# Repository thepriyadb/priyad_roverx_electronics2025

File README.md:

*15/05/25*
*Task 0: Evaluation of rover technologies implemented by different teams in previous years of the University Rover Challenge (URC)*

*20/05/25*
*Task 1:* 
*Communication protocols - I2C, CAN, Relays*

*26/05/25*
*Task 1:* 
- *SSR*
- *Octocoupler*
- *Differential pair*
- *Arbitration*
- *CRC*

*2/06/25*
*Task 2:*
1. *Start with C++ basics with the W3 schools website*
2. *Start reading about an Arduino, what it is and how it functions*

*07/06/25*
*Task 3:*
- *STM32*
- *Timers & Clocks*

*08/06/25*
*Task 4:*
1. *Compare microcontrollers*
2. *PWM Signal Wave Visualization*

*17/06/25*
*Task 5:*
- *PWM*
- *Projects on Arduino*
- *Delays vs Millis*

*21/05/2025*
*Task 6:*
*Register level programming*

*15/07/2025*
*Task 7:*
*Design a schematic with a fan, an LED and Arduino using KiCAD*

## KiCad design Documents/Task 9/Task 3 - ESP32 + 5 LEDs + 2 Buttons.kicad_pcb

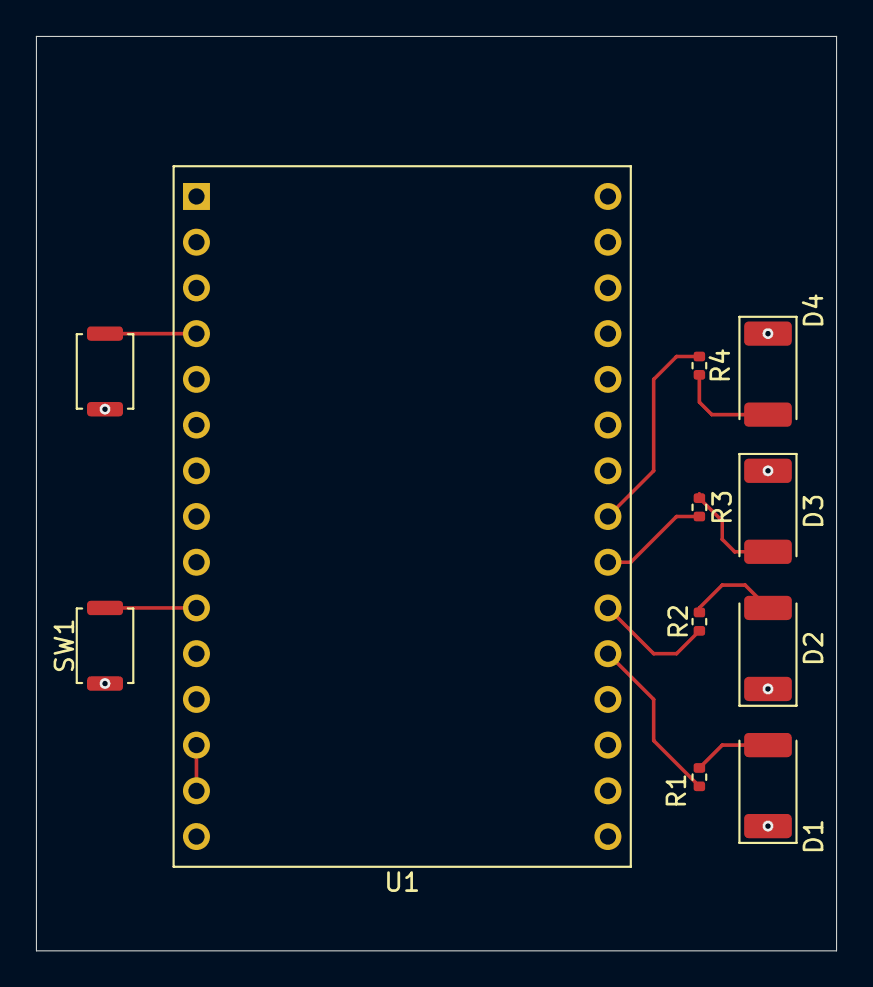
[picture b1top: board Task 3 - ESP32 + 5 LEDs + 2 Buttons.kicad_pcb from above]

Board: 2 copper layers, 44.4 x 50.8 mm, 11 parts (0 on the bottom side), 12 nets.

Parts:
D1, D2, D3, D4: LED; LED_2010_5025Metric
R1, R2, R3, R4: R; R_0402_1005Metric
SW1, SW2: SW_Push; SW_Push_SPST_NO_Alps_SKRK
U1: ESP32-C3-DevKitM-1

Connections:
+5V: U1.13 (5V), U1.14 (5V)
/LED1: R1.1, U1.20 (IO4)
/LED2: R2.1, U1.21 (IO5)
/LED3: R3.1, U1.22 (IO6)
/LED4: R4.1, U1.23 (IO7)
/SW1: SW1.2, U1.10 (IO1)
/SW2: SW2.1, U1.4 (IO2)
GND: D1.1 (K), D2.1 (K), D3.1 (K), D4.1 (K), SW1.1, SW2.2, U1.1 (GND), U1.6 (GND), U1.8 (GND), U1.12 (GND), U1.15 (GND), U1.16 (GND), U1.19 (GND), U1.24 (GND), U1.27 (GND), U1.30 (GND)
unnamed: D1.2 (A), R1.2
unnamed: D2.2 (A), R2.2
unnamed: D3.2 (A), R3.2
unnamed: D4.2 (A), R4.2

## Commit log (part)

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2025-05-29 Initial commit of Obsidian notes
2025-05-30 Update notes
2025-06-07 Updated notes
2025-06-07 images
2025-06-17 removal
2025-07-27 Create Task 9 - ESP32 + 4 LEDs + 2 Switches
2025-07-27 Update Task 9 - ESP32 + 4 LEDs + 2 Switches
2025-07-28 Rename Task 9 - ESP32 + 4 LEDs + 2 Switches to Task 9 - ESP32 + 4 LEDs + 2 Switches.md
2025-12-29 Rename .gitignore to STM32_ARM/.gitignore
2025-12-29 Arm Code Updated
2025-12-29 ARM code
